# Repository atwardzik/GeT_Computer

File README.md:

# GeT Computer

A custom-designed single-board computer built with RP2354B MCU. This project serves as a hardware platform for my experimental [operating system](https://github.com/atwardzik/os_kernel). In its form it was inspired by the original Raspberry Pi SBC. However, it features an MCU that is much more managable in terms of low level development, as it is provided with comprehensive [datasheet](https://pip-assets.raspberrypi.com/categories/1214-rp2350/documents/RP-008373-DS-2-rp2350-datasheet.pdf?disposition=inline) covering all details. Additionally, the board includes hardware interfaces (VGA, PS2, microSD) specifically selected for their simplicity in driver implementation. The board also features Ethernet chip by WIZNet and slot for soldering Raspberry Pi Radio Module.

This repository contains the **hardware design files** (KiCad schematics, PCB layout, BOM).

## What's in This Repository

- **KiCad Project Files** (`.kicad_pcb`, `.kicad_sch`, `.kicad_pro`)
- **Bill of Materials (BOM)**
- **Gerber Files** for manufacturing

## Visual Overview

### Schematic

### KiCad Design View

### Physical PCB

## Hardware Specifications

| Feature | Specification |
|---------|---------------|
| Processor | RP2354B |
| RAM | 520KB internal SRAM + 8MB external PSRAM |
| Non-volatile storage | microSD Card |
| Ethernet | WIZnet W5100S |
| WiFi and Bluetooth | Raspberry Pi Radio Module 2 (RM2) |
| IO | VGA@640x480 and PS2 keyboard |
| Power Input | 5V @ 1A |
| Dimensions | 85mm x 56mm x 17mm |
| Stackup | 4-layer with power and ground planes |

## Viewing the Design
1. Install [KiCad](https://www.kicad.org/) (version [9.0+])
2. Open `GeT_Computer.kicad_pro`
3. Explore schematics and PCB layout

## Software

This hardware was designed specifically for the [GeT OS](https://github.com/atwardzik/os_kernel). The OS repo contains:
- Kernel code
- Drivers for peripherals.
- Build instructions

## Contributing
Although the project is already manufactured, feel free to open any issues regarding problems you may have found.

## License
CC BY-NC-SA 4.0

Copyright (c) 2026, Artur Twardzik

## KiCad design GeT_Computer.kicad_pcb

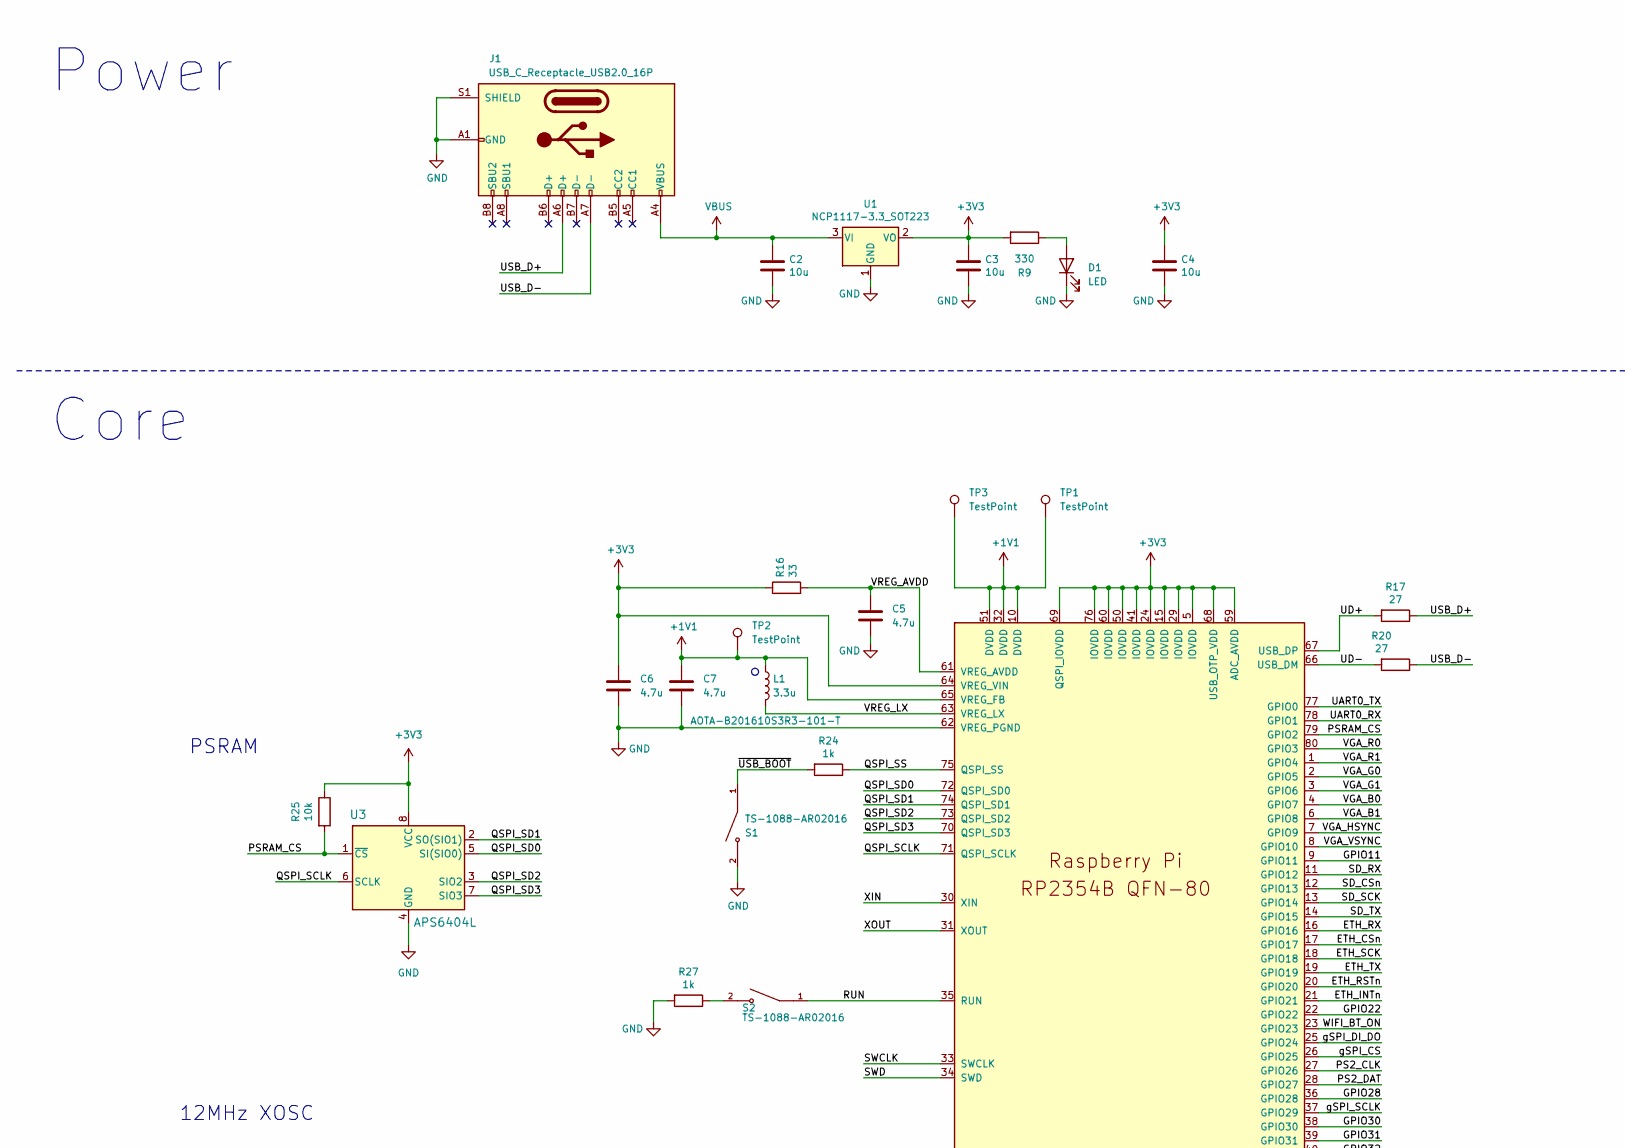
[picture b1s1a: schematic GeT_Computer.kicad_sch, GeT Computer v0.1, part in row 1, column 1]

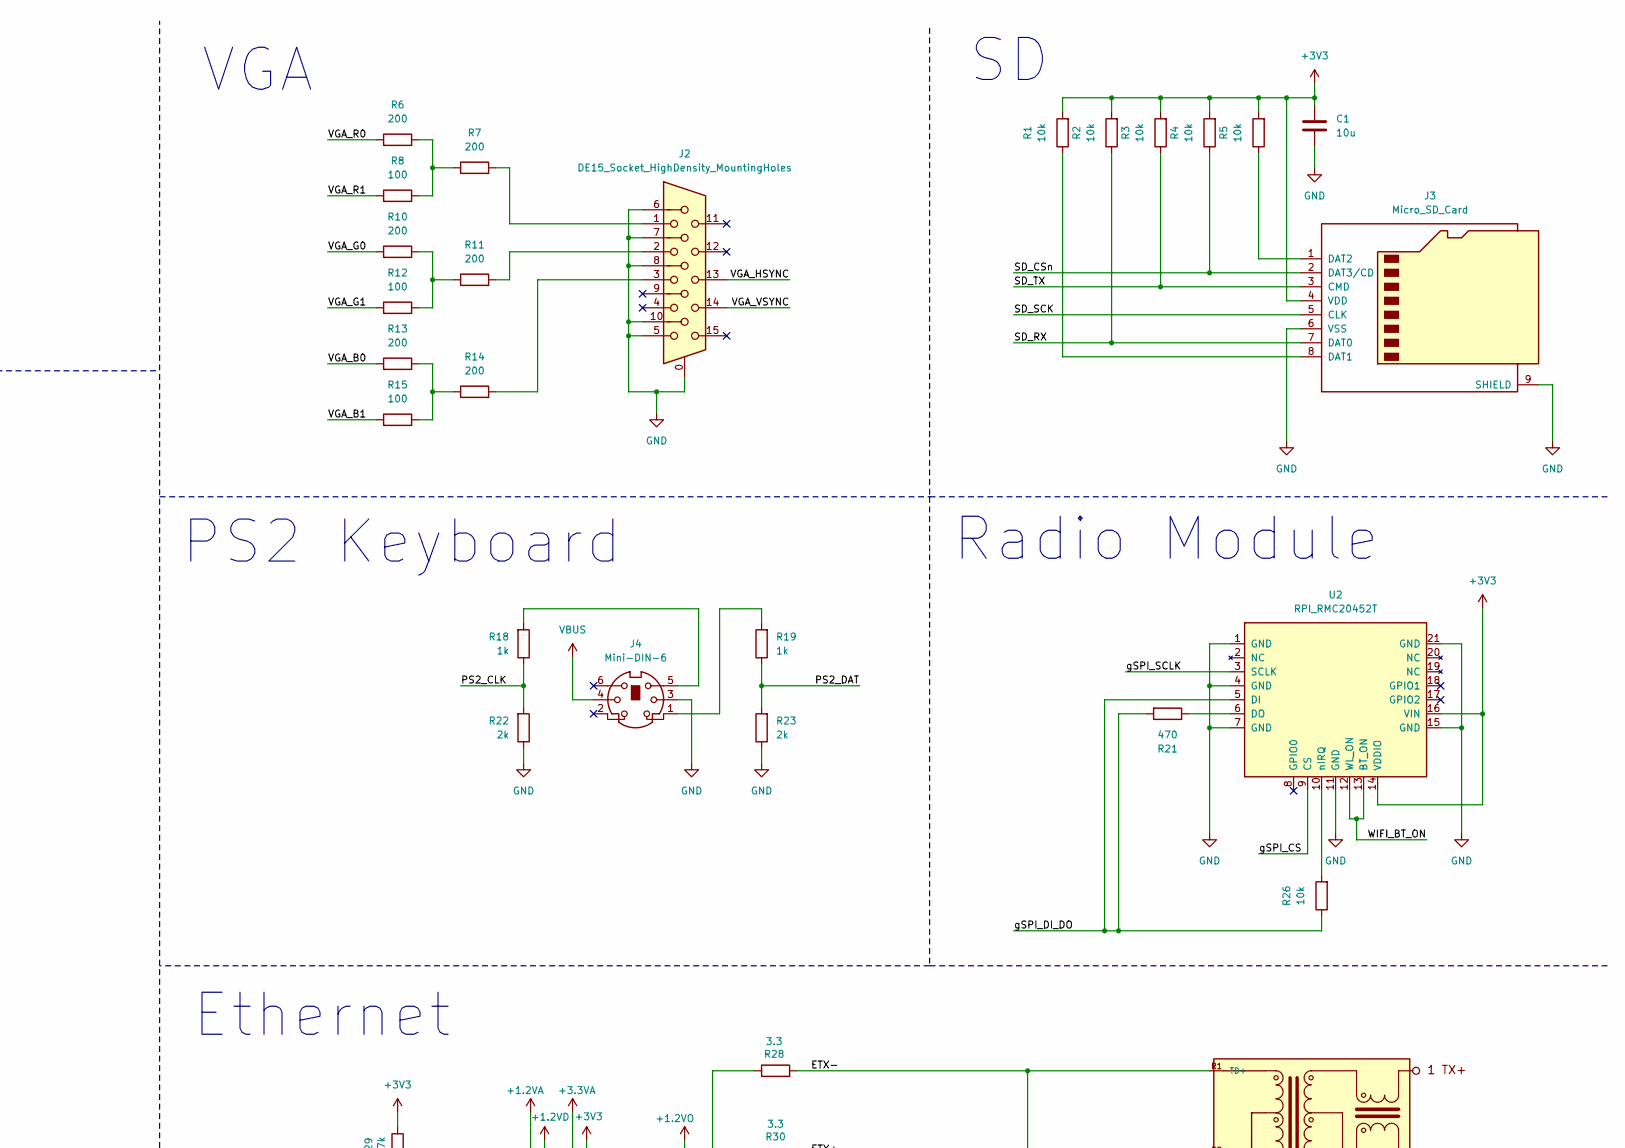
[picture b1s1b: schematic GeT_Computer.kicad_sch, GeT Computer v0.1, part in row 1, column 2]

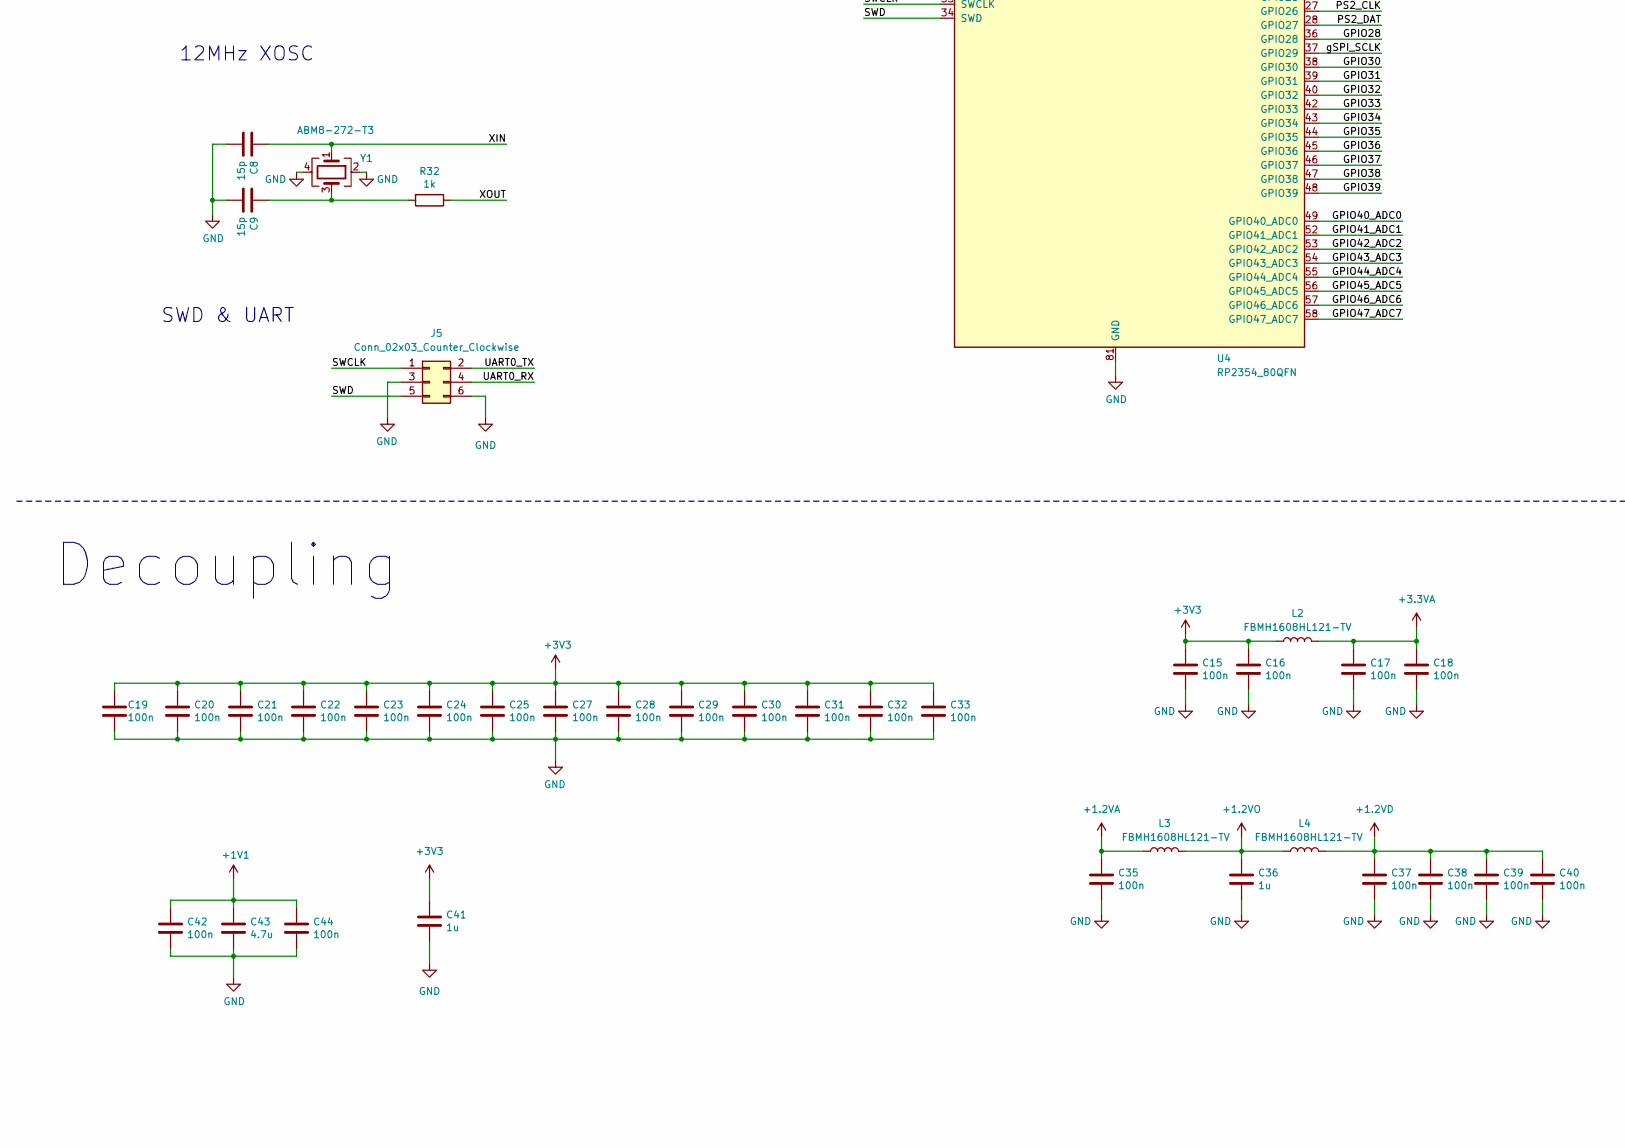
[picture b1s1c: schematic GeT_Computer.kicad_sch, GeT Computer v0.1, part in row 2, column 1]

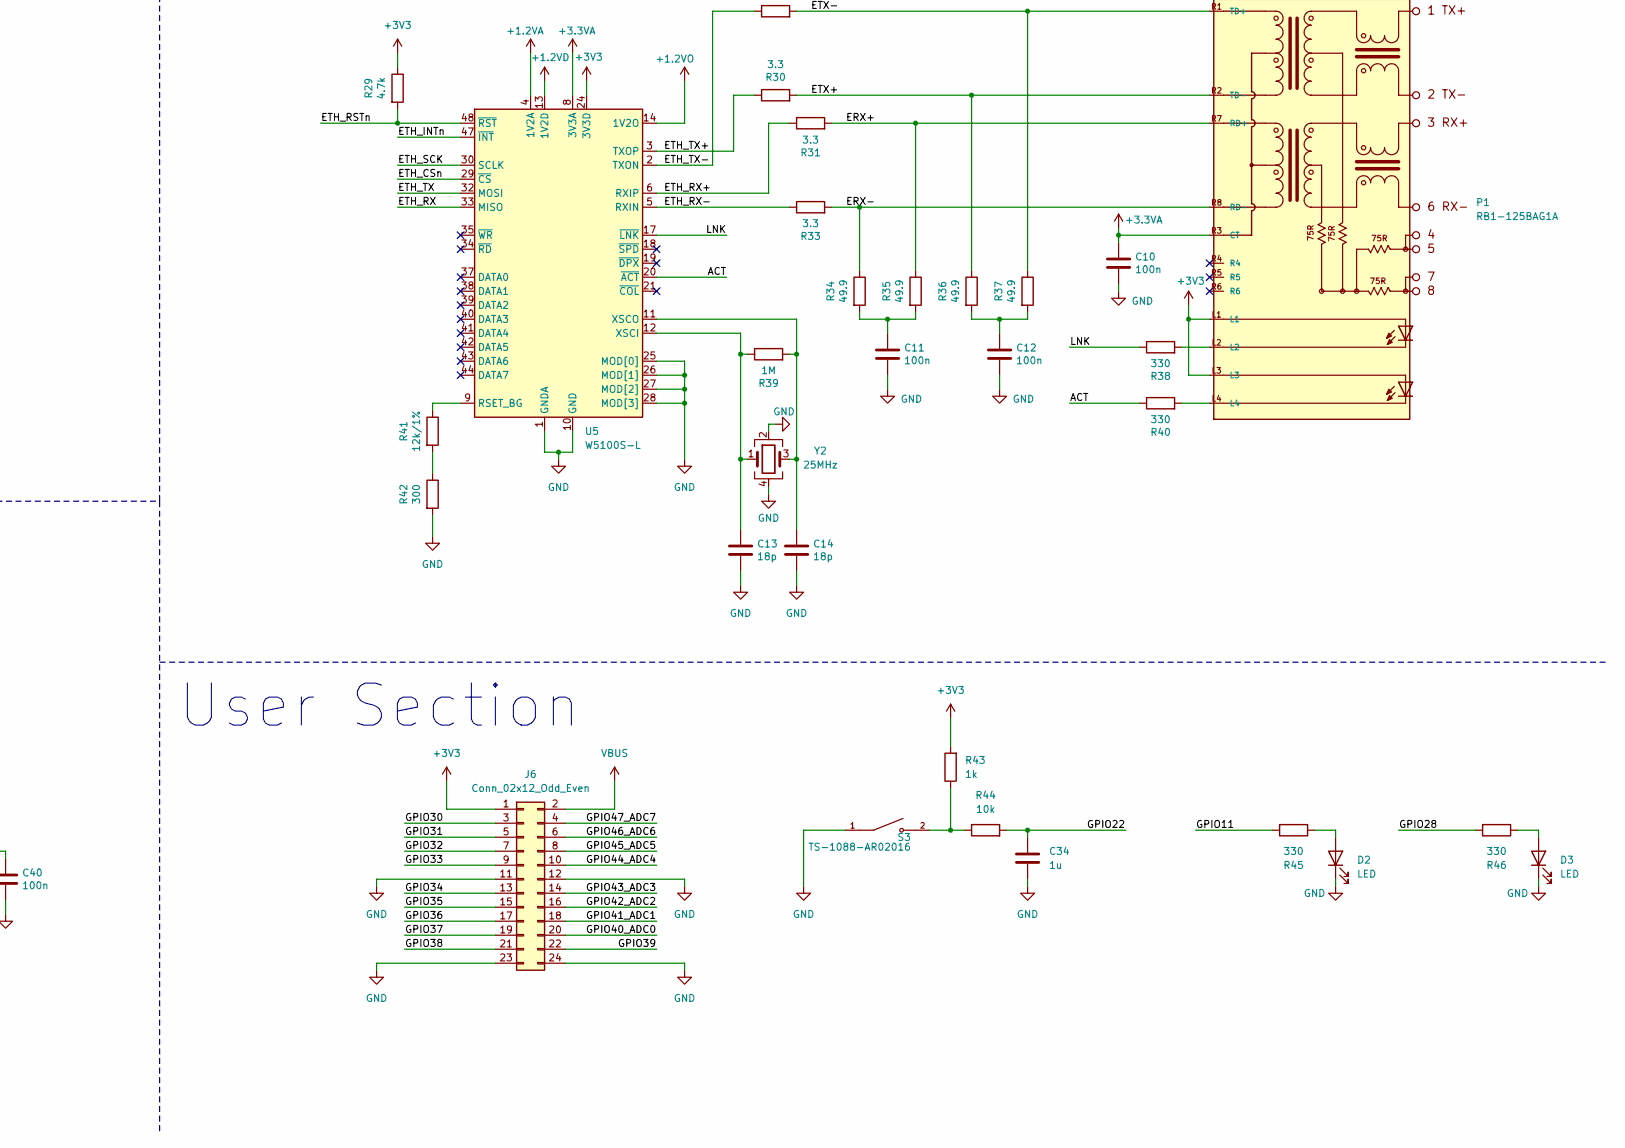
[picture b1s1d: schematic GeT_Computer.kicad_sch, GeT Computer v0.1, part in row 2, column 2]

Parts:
C1, C2, C3, C4: 10u; C_0805_2012Metric_Pad1.18x1.45mm_HandSolder
C5, C43: 4.7u; C_0402_1005Metric
C6, C7: 4.7u; C_0402_1005Metric_small_pads
C8, C9: 15p; C_0402_1005Metric
C10, C11, C12, C15, C16, C17, C18, C19, C20, C21, C22, C23, C24, C25, C27, C28, C29, C30, C31, C32, C33, C35, C37, C38, C39, C40, C42, C44: 100n; C_0402_1005Metric
C13, C14: 18p; C_0402_1005Metric
C34: 1u; C_0805_2012Metric_Pad1.18x1.45mm_HandSolder
C36: 1u; C_0805_2012Metric
C41: 1u; C_0402_1005Metric
D1, D2, D3: LED; LED_0805_2012Metric_Pad1.15x1.40mm_HandSolder
J1: USB_C_Receptacle_USB2.0_16P; USB-C_SMD-TYPE-C-31-M-12
J2: DE15_Socket_HighDensity_MountingHoles; DSUB-15-HD_Socket_Horizontal_P2.29x2.54mm_EdgePinOffset8.35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
J3: Micro_SD_Card; microSD_HC_Molex_104031-0811
J4: Mini-DIN-6; mini-din-6
J5: Conn_02x03_Counter_Clockwise; PinHeader_2x03_P2.54mm_Vertical
J6: Conn_02x12_Odd_Even; PinHeader_2x12_P2.54mm_Vertical
L1: 3.3u; L_pol_2016
L2, L3, L4: FBMH1608HL121-TV; L_0603_1608Metric
P1: RB1-125BAG1A; WIZNET_RB1-125BAG1A
R1, R2, R3, R4, R5, R26, R44: 10k; R_0805_2012Metric_Pad1.20x1.40mm_HandSolder
R6, R7, R10, R11, R13, R14: 200; R_0805_2012Metric_Pad1.20x1.40mm_HandSolder
R8, R12, R15: 100; R_0805_2012Metric_Pad1.20x1.40mm_HandSolder
R9, R45, R46: 330; R_0805_2012Metric_Pad1.20x1.40mm_HandSolder
R16: 33; R_0402_1005Metric
R17, R20: 27; R_0402_1005Metric
R18, R19, R43: 1k; R_0805_2012Metric_Pad1.20x1.40mm_HandSolder
R21: 470; R_0805_2012Metric_Pad1.20x1.40mm_HandSolder
R22, R23: 2k; R_0805_2012Metric_Pad1.20x1.40mm_HandSolder
R24, R27, R32: 1k; R_0402_1005Metric
R25: 10k; R_0402_1005Metric
R28, R30, R31, R33: 3.3; R_0402_1005Metric
R29: 4.7k; R_0402_1005Metric
R34, R35, R36, R37: 49.9; R_0402_1005Metric
R38, R40: 330; R_0402_1005Metric
R39: 1M; R_0402_1005Metric
R41: 12k/1%; R_0402_1005Metric
R42: 300; R_0402_1005Metric
S1, S2, S3: TS-1088-AR02016; SW_TS-1088-AR02016; PARTREV N/A
TP1, TP2, TP3: TestPoint; TestPoint_Pad_D2.0mm
U1: NCP1117-3.3_SOT223; SOT-223-3_TabPin2
U2: RPI_RMC20452T; rpi_rmc20452t
U3: APS6404L; SOP-8_3.9x4.9mm_P1.27mm
U4: RP2354_80QFN; RP2354-QFN-80-1EP_10x10_P0.4mm_EP3.4x3.4mm_ThermalVias_1
U5: W5100S-L; LQFP-48_7x7mm_P0.5mm
Y1: ABM8-272-T3; Crystal_SMD_3225-4Pin_3.2x2.5mm
Y2: 25MHz; Crystal_SMD_3225-4Pin_3.2x2.5mm

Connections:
+1.2VA: C35.1, L3.1, U5.4 (1V2A)
+1.2VD: C37.1, C38.1, C39.1, C40.1, L4.2, U5.13 (1V2D), U5.22 (1V2D), U5.31 (1V2D), U5.45 (1V2D)
+1.2VO: C36.1, L3.2, L4.1, U5.14 (1V2O)
+1V1: C7.1, C42.1, C43.1, C44.1, L1.1, TP1.1, TP2.1, TP3.1, U4.10 (DVDD), U4.32 (DVDD), U4.51 (DVDD), U4.65 (VREG_FB)
+3.3VA: C10.1, C17.1, C18.1, L2.2, P1.R3 (CT), U5.8 (3V3A), U5.15 (3V3A)
+3V3: C1.1, C3.1, C4.1, C6.1, C15.1, C16.1, C19.1, C20.1, C21.1, C22.1, C23.1, C24.1, C25.1, C27.1, C28.1, C29.1, C30.1, C31.1, C32.1, C33.1, C41.1, J3.4 (VDD), J6.1, L2.1, P1.L1, P1.L3, R1.2, R2.2, R3.2, R4.2, R5.2, R9.2, R16.1, R25.1, R29.1, R43.2, U1.2 (VO), U2.14 (VDDIO), U2.16 (VIN), U3.8 (VCC), U4.5 (IOVDD), U4.15 (IOVDD), U4.24 (IOVDD), U4.29 (IOVDD), U4.41 (IOVDD), U4.50 (IOVDD), U4.59 (ADC_AVDD), U4.60 (IOVDD), U4.64 (VREG_VIN), U4.68 (USB_OTP_VDD), U4.69 (QSPI_IOVDD), U4.76 (IOVDD), U5.24 (3V3D), U5.36 (3V3D)
/ACT: R40.1, U5.20 (~ACT)
/ERX+: P1.R7 (RD+), R31.2, R35.1
/ERX-: P1.R8 (RD-), R33.2, R34.1
/ETH_CSn: U4.17 (GPIO17), U5.29 (~CS)
/ETH_INTn: U4.21 (GPIO21), U5.47 (~INT)
/ETH_RSTn: R29.2, U4.20 (GPIO20), U5.48 (~RST)
/ETH_RX: U4.16 (GPIO16), U5.33 (MISO)
/ETH_RX+: R31.1, U5.6 (RXIP)
/ETH_RX-: R33.1, U5.5 (RXIN)
/ETH_SCK: U4.18 (GPIO18), U5.30 (SCLK)
/ETH_TX: U4.19 (GPIO19), U5.32 (MOSI)
/ETH_TX+: R30.1, U5.3 (TXOP)
/ETH_TX-: R28.1, U5.2 (TXON)
/ETX+: P1.R2 (TD-), R30.2, R36.1
/ETX-: P1.R1 (TD+), R28.2, R37.1
/GPIO11: R45.2, U4.9 (GPIO11)
/GPIO22: C34.1, R44.2, U4.22 (GPIO22)
/GPIO28: R46.2, U4.36 (GPIO28)
/GPIO30: J6.3, U4.38 (GPIO30)
/GPIO31: J6.5, U4.39 (GPIO31)
/GPIO32: J6.7, U4.40 (GPIO32)
/GPIO33: J6.9, U4.42 (GPIO33)
/GPIO34: J6.13, U4.43 (GPIO34)
/GPIO35: J6.15, U4.44 (GPIO35)
/GPIO36: J6.17, U4.45 (GPIO36)
/GPIO37: J6.19, U4.46 (GPIO37)
/GPIO38: J6.21, U4.47 (GPIO38)
/GPIO39: J6.22, U4.48 (GPIO39)
/GPIO40_ADC0: J6.20, U4.49 (GPIO40_ADC0)
/GPIO41_ADC1: J6.18, U4.52 (GPIO41_ADC1)
/GPIO42_ADC2: J6.16, U4.53 (GPIO42_ADC2)
/GPIO43_ADC3: J6.14, U4.54 (GPIO43_ADC3)
/GPIO44_ADC4: J6.10, U4.55 (GPIO44_ADC4)
/GPIO45_ADC5: J6.8, U4.56 (GPIO45_ADC5)
/GPIO46_ADC6: J6.6, U4.57 (GPIO46_ADC6)
/GPIO47_ADC7: J6.4, U4.58 (GPIO47_ADC7)
/LNK: R38.1, U5.17 (~LNK)
/PS2_CLK: R18.1, R22.2, U4.27 (GPIO26)
/PS2_DAT: R19.1, R23.2, U4.28 (GPIO27)
/PSRAM_CS: R25.2, U3.1 (~CS), U4.79 (GPIO2)
/QSPI_SCLK: U3.6 (SCLK), U4.71 (QSPI_SCLK)
/QSPI_SD0: U3.5 (SI(SIO0)), U4.72 (QSPI_SD0)
/QSPI_SD1: U3.2 (SO(SIO1)), U4.74 (QSPI_SD1)
/QSPI_SD2: U3.3 (SIO2), U4.73 (QSPI_SD2)
/QSPI_SD3: U3.7 (SIO3), U4.70 (QSPI_SD3)
/QSPI_SS: R24.1, U4.75 (QSPI_SS)
/RUN: S2.1, U4.35 (RUN)
/SD_CSn: J3.2 (DAT3/CD), R4.1, U4.12 (GPIO13)
/SD_RX: J3.7 (DAT0), R2.1, U4.11 (GPIO12)
/SD_SCK: J3.5 (CLK), U4.13 (GPIO14)
/SD_TX: J3.3 (CMD), R3.1, U4.14 (GPIO15)
/SWCLK: J5.1, U4.33 (SWCLK)
/SWD: J5.5, U4.34 (SWD)
/UART0_RX: J5.4, U4.78 (GPIO1)
/UART0_TX: J5.2, U4.77 (GPIO0)
/UD+: R17.2, U4.67 (USB_DP)
/UD-: R20.2, U4.66 (USB_DM)
/USB_D+: J1.A6 (D+), R17.1
/USB_D-: J1.A7 (D-), R20.1
/VGA_B0: R13.1, U4.4 (GPIO7)
/VGA_B1: R15.1, U4.6 (GPIO8)
/VGA_G0: R10.1, U4.2 (GPIO5)
/VGA_G1: R12.1, U4.3 (GPIO6)
/VGA_HSYNC: J2.13, U4.7 (GPIO9)
/VGA_R0: R6.1, U4.80 (GPIO3)
/VGA_R1: R8.1, U4.1 (GPIO4)
/VGA_VSYNC: J2.14, U4.8 (GPIO10)
/VREG_AVDD: C5.1, R16.2, U4.61 (VREG_AVDD)
/VREG_LX: L1.2, U4.63 (VREG_LX)
/WIFI_BT_ON: U2.12 (WL_ON), U2.13 (BT_ON), U4.23 (GPIO23)
/XIN: C8.1, U4.30 (XIN), Y1.1
/XOUT: R32.1, U4.31 (XOUT)
/gSPI_CS: U2.9 (CS), U4.26 (GPIO25)
/gSPI_DI_DO: R21.2, R26.1, U2.5 (DI), U4.25 (GPIO24)
/gSPI_SCLK: U2.3 (SCLK), U4.37 (GPIO29)
/~USB_BOOT: R24.2, S1.1
GND: C1.2, C2.2, C3.2, C4.2, C5.2, C6.2, C7.2, C8.2, C9.2, C10.2, C11.2, C12.2, C13.2, C14.2, C15.2, C16.2, C17.2, C18.2, C19.2, C20.2, C21.2, C22.2, C23.2, C24.2, C25.2, C27.2, C28.2, C29.2, C30.2, C31.2, C32.2, C33.2, C34.2, C35.2, C36.2, C37.2, C38.2, C39.2, C40.2, C41.2, C42.2, C43.2, C44.2, D1.1 (K), D2.1 (K), D3.1 (K), J1.A1 (GND), J1.A12 (GND), J1.B1 (GND), J1.B12 (GND), J1.S1 (SHIELD), J2.0, J2.5, J2.6, J2.7, J2.8, J2.10, J3.6 (VSS), J3.9 (SHIELD), J4.3, J5.3, J5.6, J6.11, J6.12, J6.23, J6.24, R22.1, R23.1, R27.2, R42.2, S1.2, S3.1, U1.1 (GND), U2.1 (GND), U2.4 (GND), U2.7 (GND), U2.11 (GND), U2.15 (GND), U2.21 (GND), U3.4 (GND), U4.62 (VREG_PGND), U4.81 (GND), U5.1 (GNDA), U5.7 (GNDA), U5.10 (GND), U5.16 (GNDA), U5.23 (GND), U5.25 (MOD[0]), U5.26 (MOD[1]), U5.27 (MOD[2]), U5.28 (MOD[3]), U5.46 (GND), Y1.2, Y1.4, Y2.2, Y2.4
unnamed: C9.1, R32.2, Y1.3
unnamed: C11.1, R34.2, R35.2
unnamed: C12.1, R36.2, R37.2
unnamed: D1.2 (A), R9.1
unnamed: D2.2 (A), R45.1
unnamed: D3.2 (A), R46.1
unnamed: J2.1, R7.2
unnamed: J2.2, R11.2
unnamed: J2.3, R14.2
unnamed: J3.8 (DAT1), R1.1
unnamed: J3.1 (DAT2), R5.1
unnamed: J4.1, R19.2
unnamed: J4.5, R18.2
unnamed: P1.L2, R38.2
unnamed: P1.L4, R40.2
unnamed: R6.2, R7.1, R8.2
unnamed: R10.2, R11.1, R12.2
unnamed: R13.2, R14.1, R15.2
unnamed: R27.1, S2.2
unnamed: R41.2, R42.1
unnamed: R43.1, R44.1, S3.2
unnamed: R21.1, U2.6 (DO)
unnamed: R26.2, U2.10 (nIRQ)
unnamed: R41.1, U5.9 (RSET_BG)
unnamed: C13.1, R39.1, U5.12 (XSCI), Y2.1
unnamed: C14.1, R39.2, U5.11 (XSCO), Y2.3
VBUS: C2.1, J1.A4 (VBUS), J1.A9 (VBUS), J1.B4 (VBUS), J1.B9 (VBUS), J4.4, J6.2, U1.3 (VI)

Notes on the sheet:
VGA
12MHz XOSC
SWD & UART
Power
PS2 Keyboard
Core
Ethernet
User Section
Decoupling
Radio Module
PSRAM

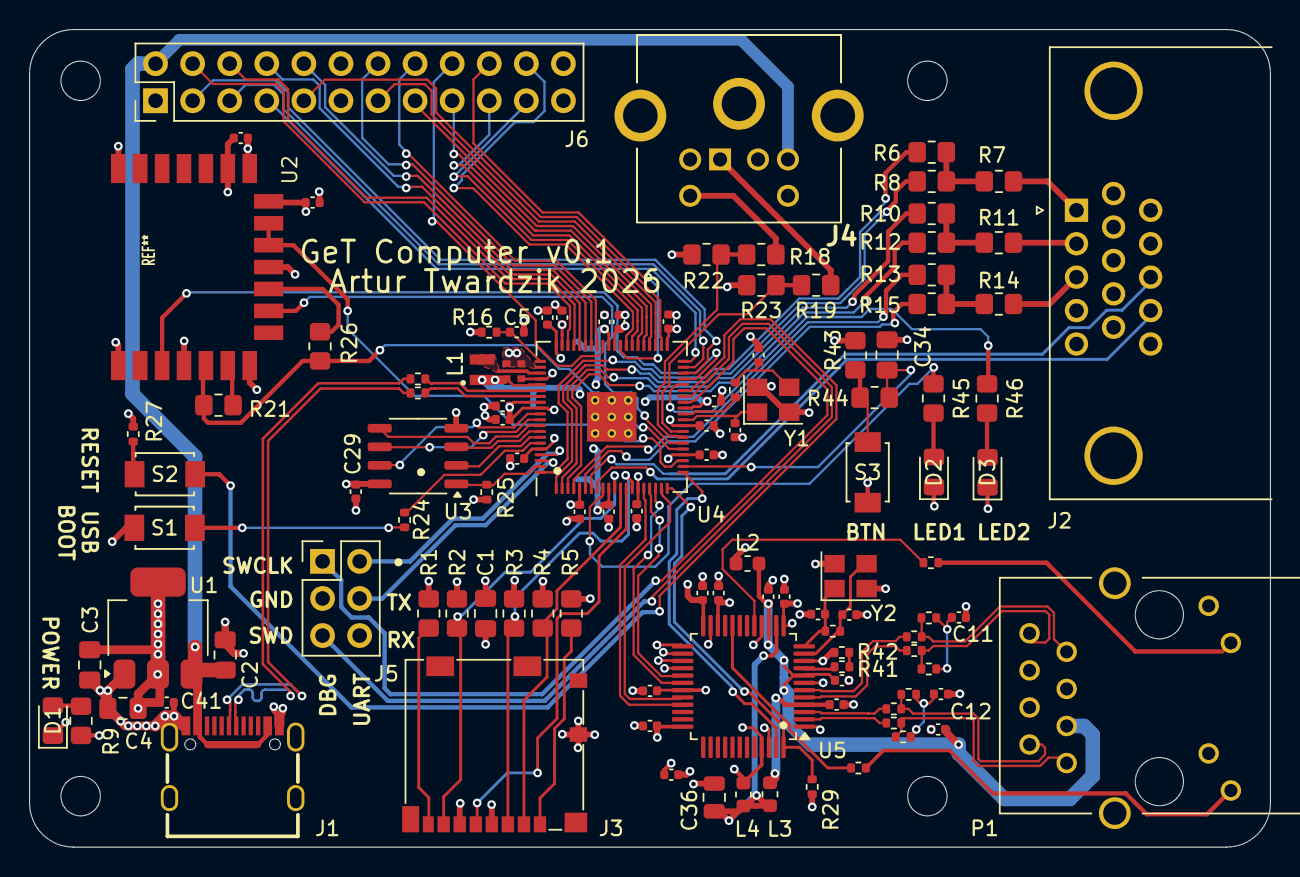
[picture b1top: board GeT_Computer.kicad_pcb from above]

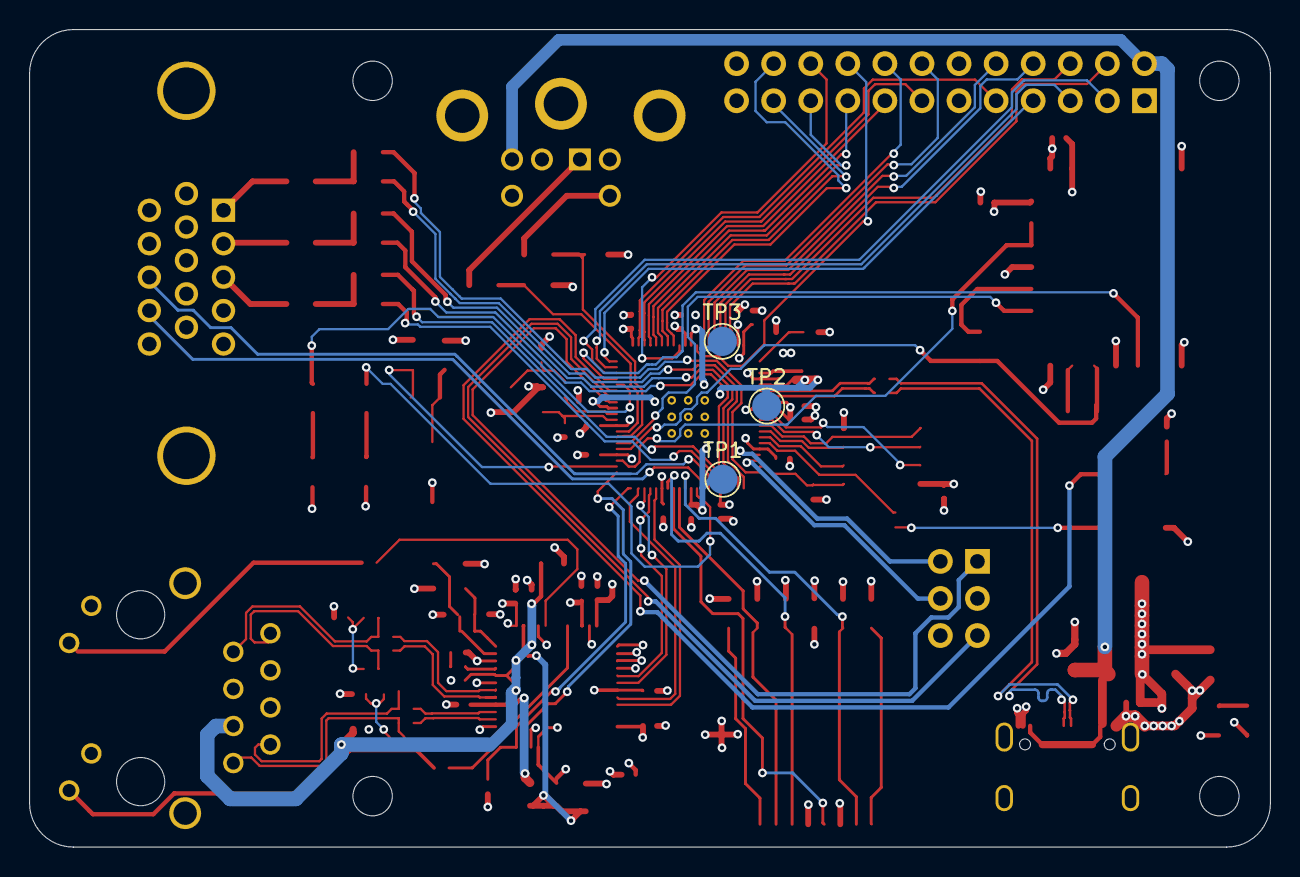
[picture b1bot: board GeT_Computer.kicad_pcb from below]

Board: 4 copper layers, 85.0 x 56.0 mm, 116 parts (3 on the bottom side), 110 nets.

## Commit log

2026-01-05 Update Schematic
2026-03-23 Add final version of the project that was printed and assembled
2026-03-23 Add fabrication output
2026-03-23 Add schematic to README
